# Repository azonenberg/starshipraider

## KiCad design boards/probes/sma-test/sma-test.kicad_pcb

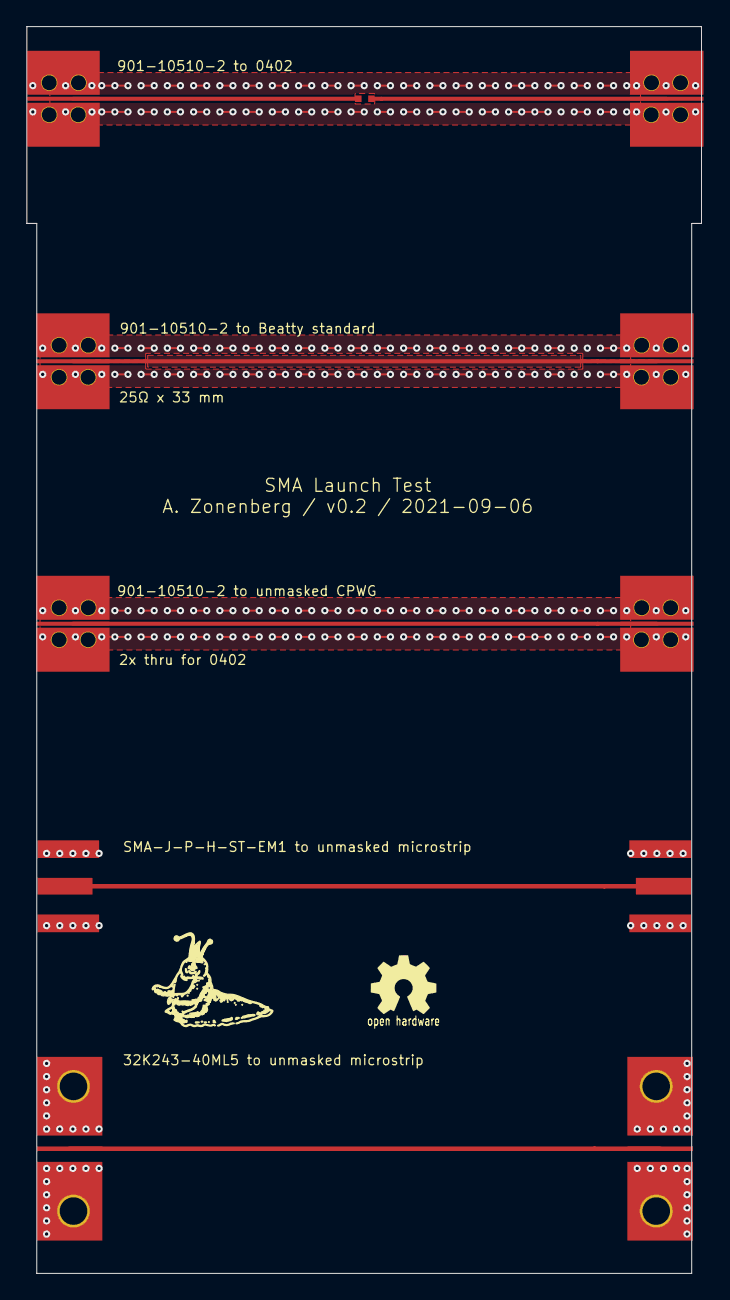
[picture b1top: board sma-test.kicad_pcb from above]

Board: 4 copper layers, 51.4 x 95.0 mm, 11 parts (0 on the bottom side), 7 nets.

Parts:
J1, J2, J3, J4, J5, J6: 901-10510-2; CONN_SMA_EDGE_AMPHENOL_901_10510-2
J11, J13: SMA-J-P-H-ST-EM1; CONN_SMA_EDGE_SAMTEC_SMA_J_P_H_ST_EM1
J12, J14: 32K243-40ML5; CONN_SMA_EDGE_ROSENBERGER_32K243_40ML5
R1: R; EIA_0402_RES_NOSILK

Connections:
/GND: J1.2, J2.2, J3.2, J4.2, J5.2, J6.2, J11.2, J12.2, J13.2, J14.2
/SIG1: J1.1, J3.1
/SIG2: J2.1, J5.1
/SIG3: J11.1, J13.1
/SIG4: J12.1, J14.1
/SIG5A: J4.1, R1.2
/SIG5B: J6.1, R1.1

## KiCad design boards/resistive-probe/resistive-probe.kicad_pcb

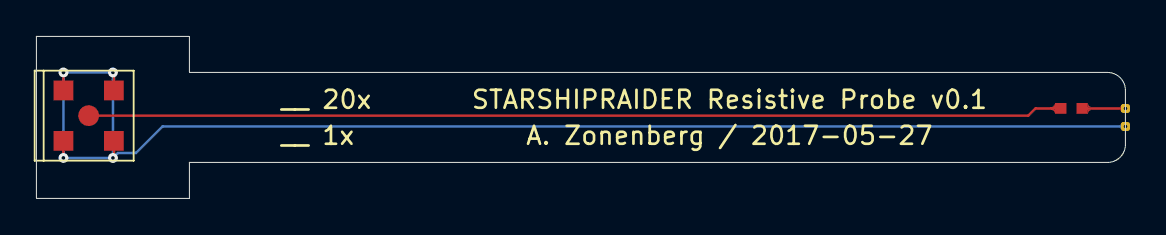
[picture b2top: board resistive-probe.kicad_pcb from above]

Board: 2 copper layers, 60.5 x 9.0 mm, 4 parts (0 on the bottom side), 3 nets.

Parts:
P1: MMCX; CONN_MMCX_LINX_CONNMMCX002SMD
P2, P3: SOLDERPAD; FLEX_SOLDERPAD
R1: R; EIA_0402_RES_NOSILK

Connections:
/GND: P1.2, P3.1
unnamed: P1.1, R1.2
unnamed: P2.1, R1.1

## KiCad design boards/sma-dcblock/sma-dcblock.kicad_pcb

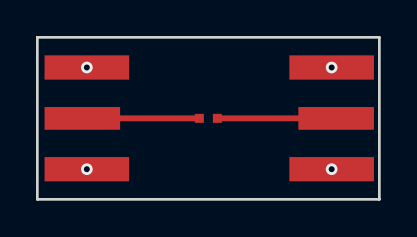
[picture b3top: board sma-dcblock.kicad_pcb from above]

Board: 4 copper layers, 19.0 x 9.0 mm, 3 parts (0 on the bottom side), 3 nets.

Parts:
C1: CL05B102KB5NCNC; EIA_0402_CAP_NOSILK
P1, P2: SMA; CONN_SMA_EDGE_SAMTEC_SMA_J_P_H_ST_EM1

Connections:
/GND: P1.2, P2.2
unnamed: C1.1, P2.1
unnamed: C1.2, P1.1

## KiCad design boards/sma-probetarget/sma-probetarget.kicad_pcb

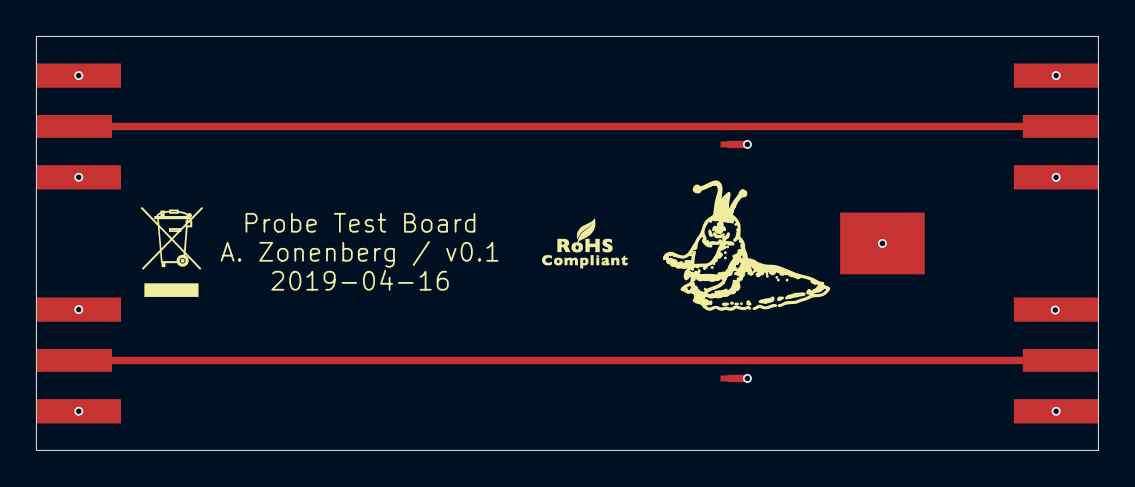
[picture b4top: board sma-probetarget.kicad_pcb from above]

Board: 4 copper layers, 59.0 x 23.0 mm, 7 parts (0 on the bottom side), 3 nets.

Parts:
J1, J2, J3, J4: Conn_Coaxial; CONN_SMA_EDGE_SAMTEC_SMA_J_P_H_ST_EM1
J5: Conn_01x01; TESTPOINT_SMT_KEYSTONE_5016
J6, J7: Conn_01x01; TESTPOINT_BARETRACE_328UM

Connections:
/FOO_N: J2.1, J4.1
/FOO_P: J1.1, J3.1
/GND: J1.2, J2.2, J3.2, J4.2, J5.1, J6.1, J7.1

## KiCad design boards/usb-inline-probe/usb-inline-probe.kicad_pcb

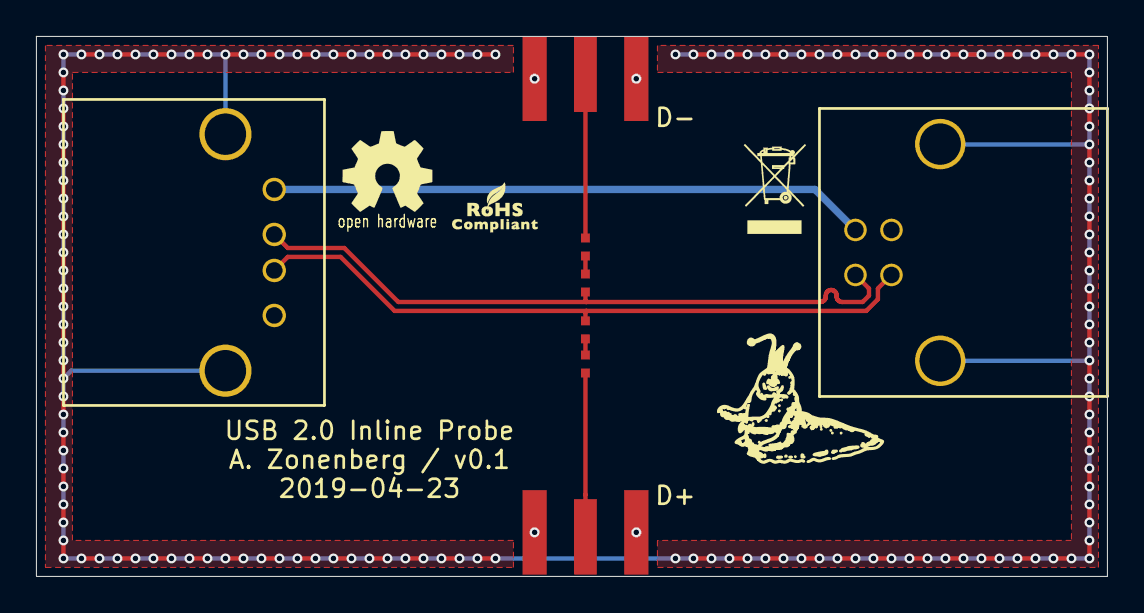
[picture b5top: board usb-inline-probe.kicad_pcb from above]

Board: 4 copper layers, 59.5 x 30.0 mm, 8 parts (0 on the bottom side), 9 nets.

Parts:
C1, C2: 0.1 uF; EIA_0402_CAP_NOSILK
J1: USB_B; CONN_USB_B_CUI_UJ2-BH-1-TH
J2: USB_A; CONN_USB_AMPHENOL_UE27AC54100
J3, J4: SMA; CONN_SMA_EDGE_SAMTEC_SMA_J_P_H_ST_EM1
R1, R2: 953; EIA_0402_RES_NOSILK

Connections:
/D_N: J1.2, J2.2, R2.2
/D_P: J1.3, J2.3, R1.2
/GND: J1.4, J2.4, J3.2, J4.2
/PROBE_N: C2.1, J4.1
/PROBE_P: C1.1, J3.1
/SHLD: J1.5, J2.5
/VBUS: J1.1, J2.1
unnamed: C1.2, R1.1
unnamed: C2.2, R2.1
